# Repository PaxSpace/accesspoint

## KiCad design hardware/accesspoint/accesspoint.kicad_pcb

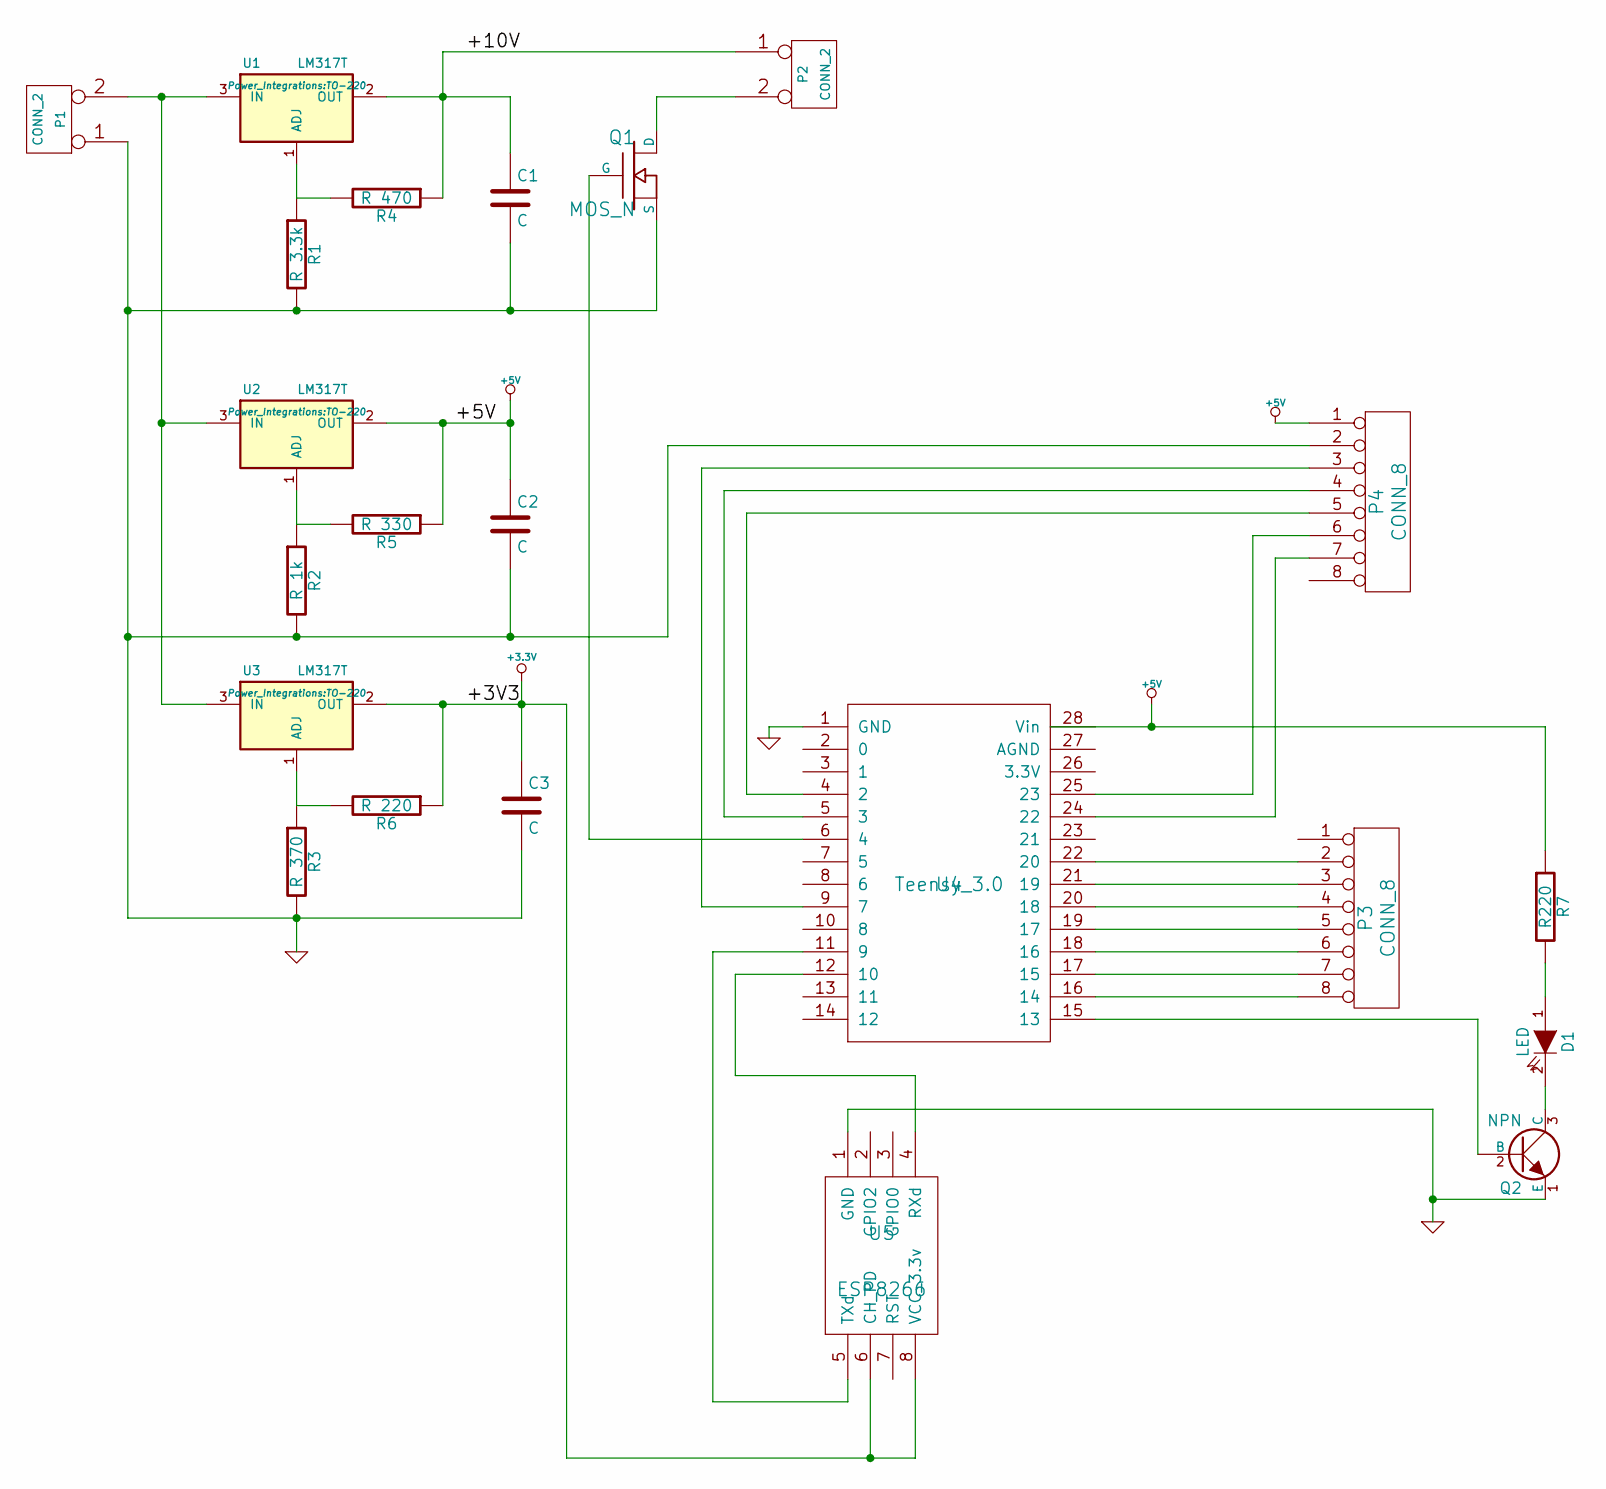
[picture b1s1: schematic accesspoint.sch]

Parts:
C1, C2, C3: C; C1
D1: LED; LED-5MM
P1, P2: CONN_2; PINHEAD1-2
P3, P4: CONN_8; RJ45_8
Q1: MOS_N
Q2: NPN
R1: R 3.3k; R3
R2: R 1k; R3
R3: R 370; R3
R4: R 470; R3
R5: R 330; R3
R6: R 220; R3
R7: R220; R3
U1, U2, U3: LM317T; TO-220
U4: Teensy_3.0; Teensy3.1
U5: ESP8266; Teensy3.1

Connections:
+3.3V: C3.1, R6.1, U3.2 (OUT), U5.6 (CH_PD), U5.8 (VCC_3.3v)
+5V: C2.1, P4.1, R5.1, R7.1, U2.2 (OUT)
/+10V: C1.1, P2.1, R4.1, U1.2 (OUT)
GND: C1.2, C2.2, C3.2, P1.1, P4.2, Q1.S, Q2.1 (E), R1.2, R2.2, R3.2, U4.1 (GND), U5.1 (GND)
unnamed: D1.1 (A), R7.2
unnamed: D1.2 (K), Q2.3 (C)
unnamed: P1.2 (PM), U1.3 (IN), U2.3 (IN), U3.3 (IN)
unnamed: P2.2 (PM), Q1.D
unnamed: P3.2, U4.22 (20)
unnamed: P3.3, U4.21 (19)
unnamed: P3.4, U4.20 (18)
unnamed: P3.5, U4.19 (17)
unnamed: P3.6, U4.18 (16)
unnamed: P3.7, U4.17 (15)
unnamed: P3.8, U4.16 (14)
unnamed: P4.3, U4.9 (7)
unnamed: P4.4, U4.5 (3)
unnamed: P4.5, U4.4 (2)
unnamed: P4.6, U4.25 (23)
unnamed: P4.7, U4.24 (22)
unnamed: Q1.G, U4.6 (4)
unnamed: Q2.2 (B), U4.15 (13)
unnamed: R1.1, R4.2, U1.1 (ADJ)
unnamed: R2.1, R5.2, U2.1 (ADJ)
unnamed: R3.1, R6.2, U3.1 (ADJ)
unnamed: U4.11 (9), U5.5 (TXd)
unnamed: U4.12 (10), U5.4 (RXd)

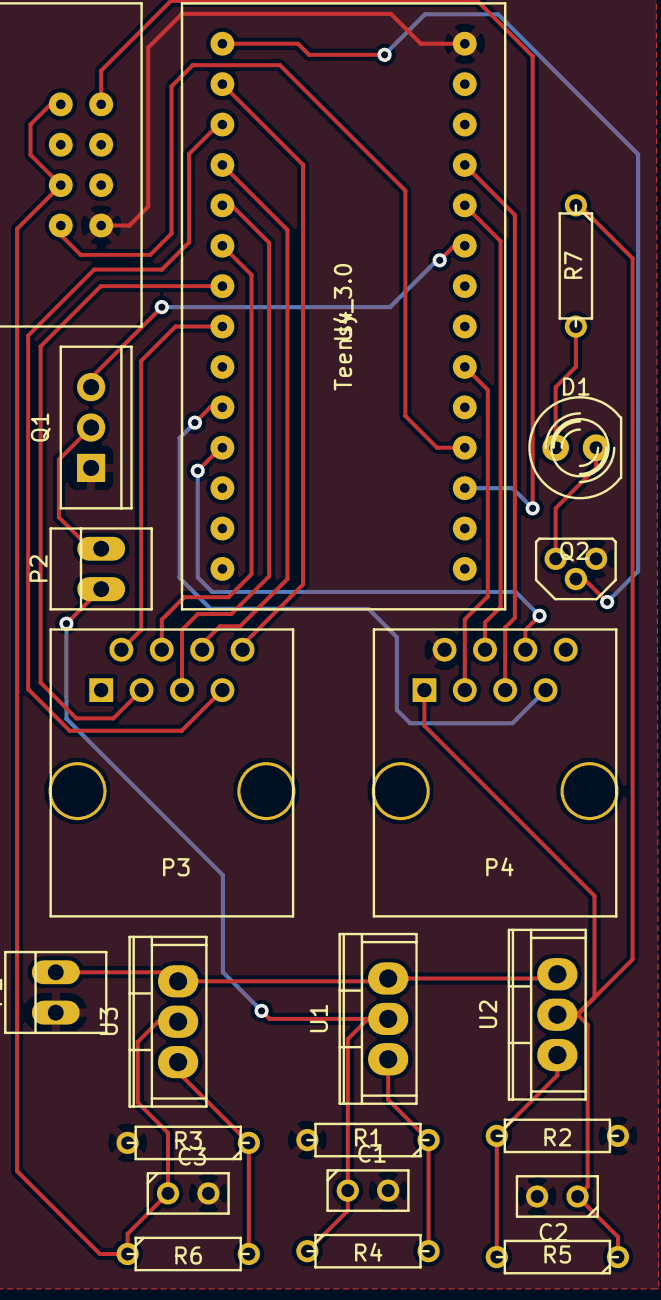
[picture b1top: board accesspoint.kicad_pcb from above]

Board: 2 copper layers, 22 parts (0 on the bottom side), 27 nets.

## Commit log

2015-04-09 fixed schematic, made netlist and more
    associated footprints with parts
    made a board (but didn't place parts or make traces)
    a lot of lessons learned
2015-04-09 added DB
2015-04-10 finished most intermediate logic
    added the necessary many-to-many db tables
    tested custom methods using curl
    still need to implement an intermediate logging route
2015-04-10 fixed board and generated top/bottom pcbs
    for some reason the files do not load correctly in kicad but works locally
    top and bottom pdfs are generated here with silks
2015-04-12 intermediate fix before v2
    check the readme for the simple electronics needed for this setup
